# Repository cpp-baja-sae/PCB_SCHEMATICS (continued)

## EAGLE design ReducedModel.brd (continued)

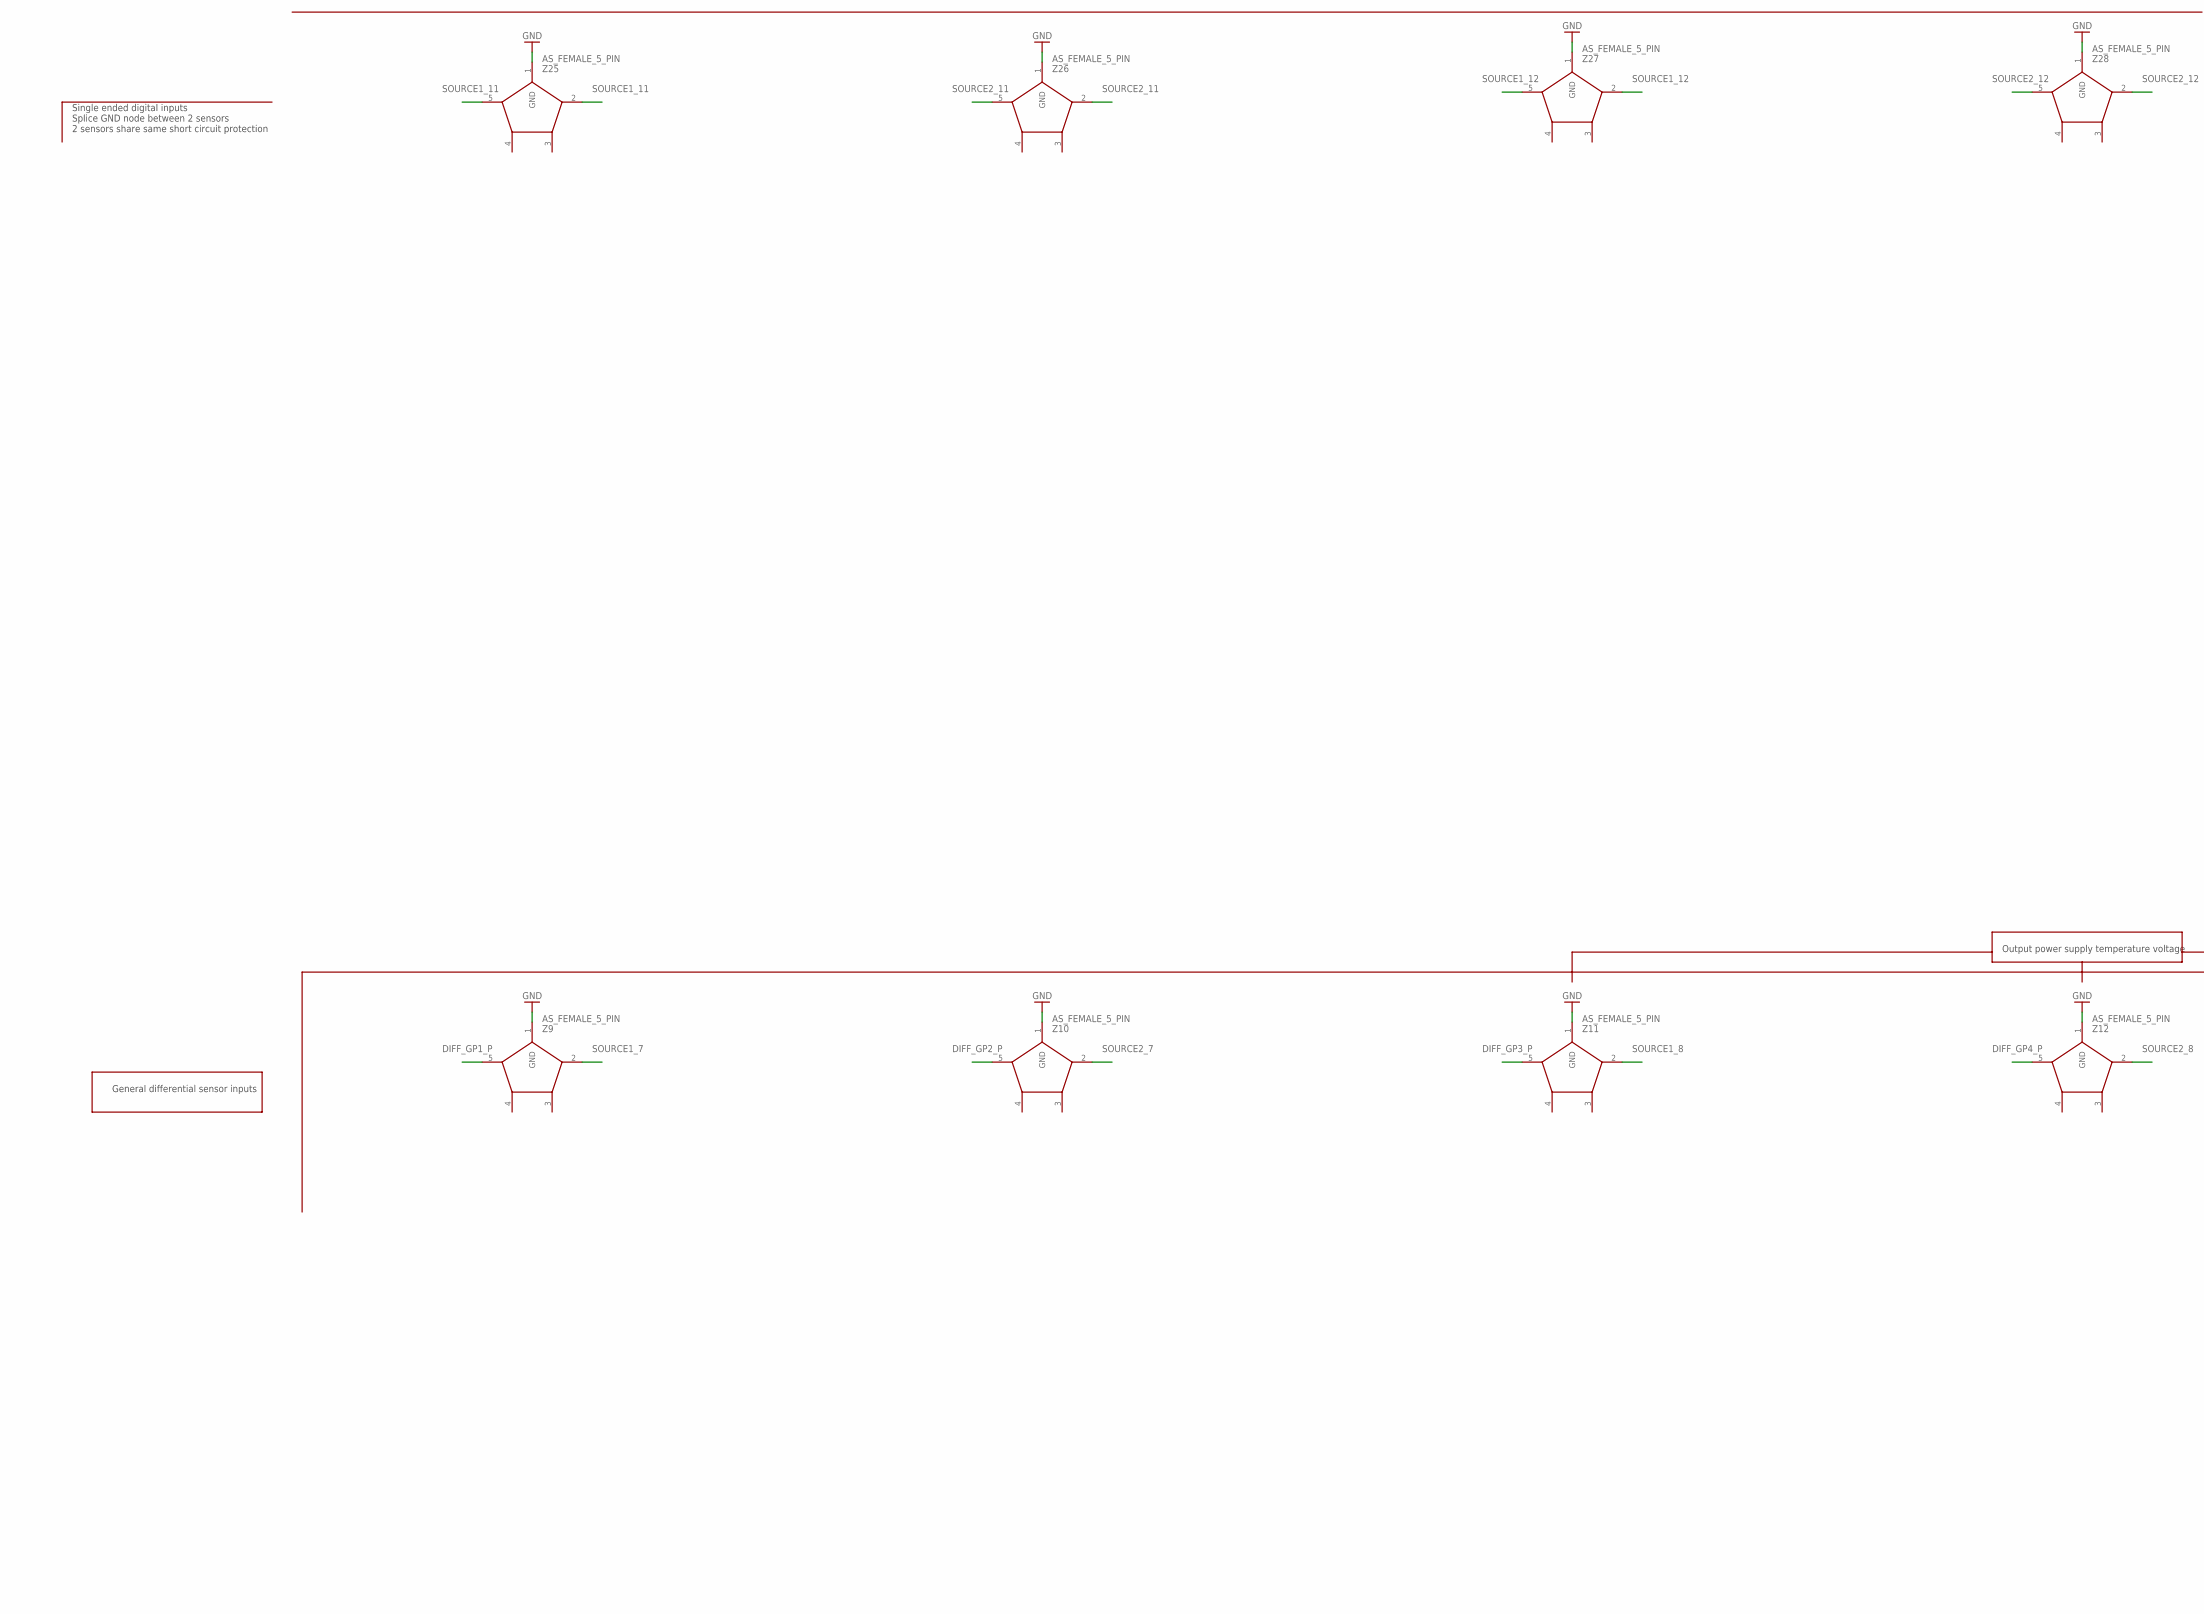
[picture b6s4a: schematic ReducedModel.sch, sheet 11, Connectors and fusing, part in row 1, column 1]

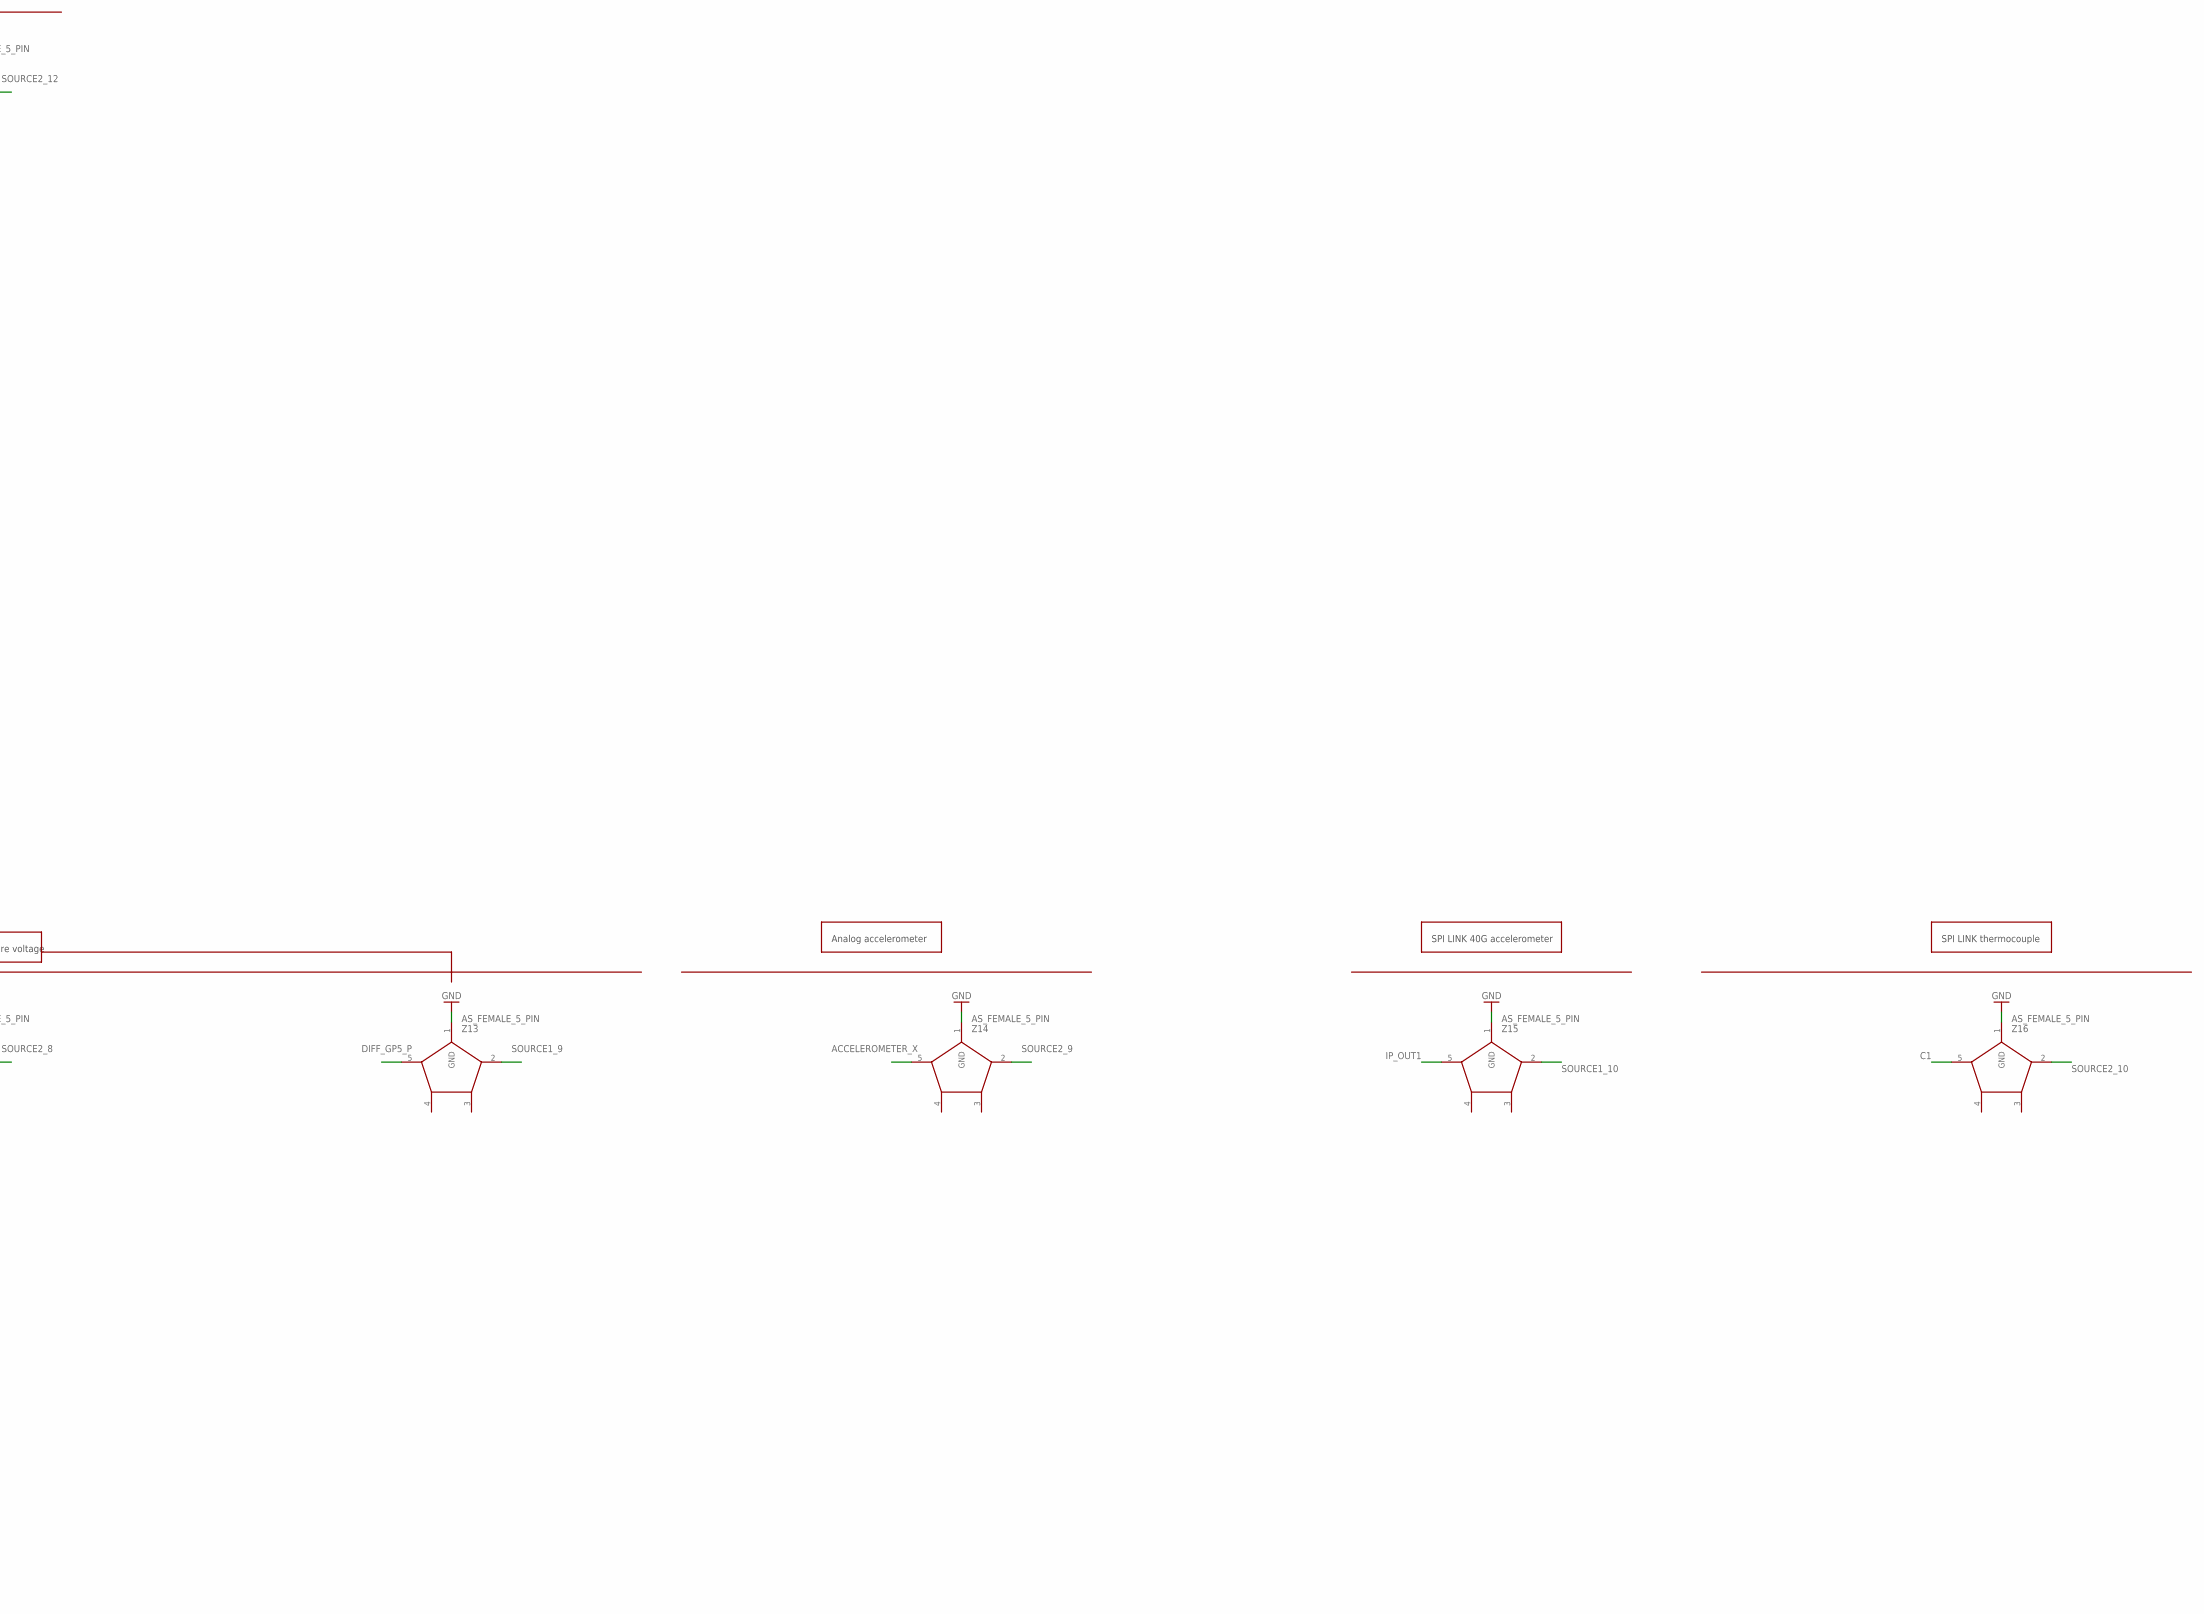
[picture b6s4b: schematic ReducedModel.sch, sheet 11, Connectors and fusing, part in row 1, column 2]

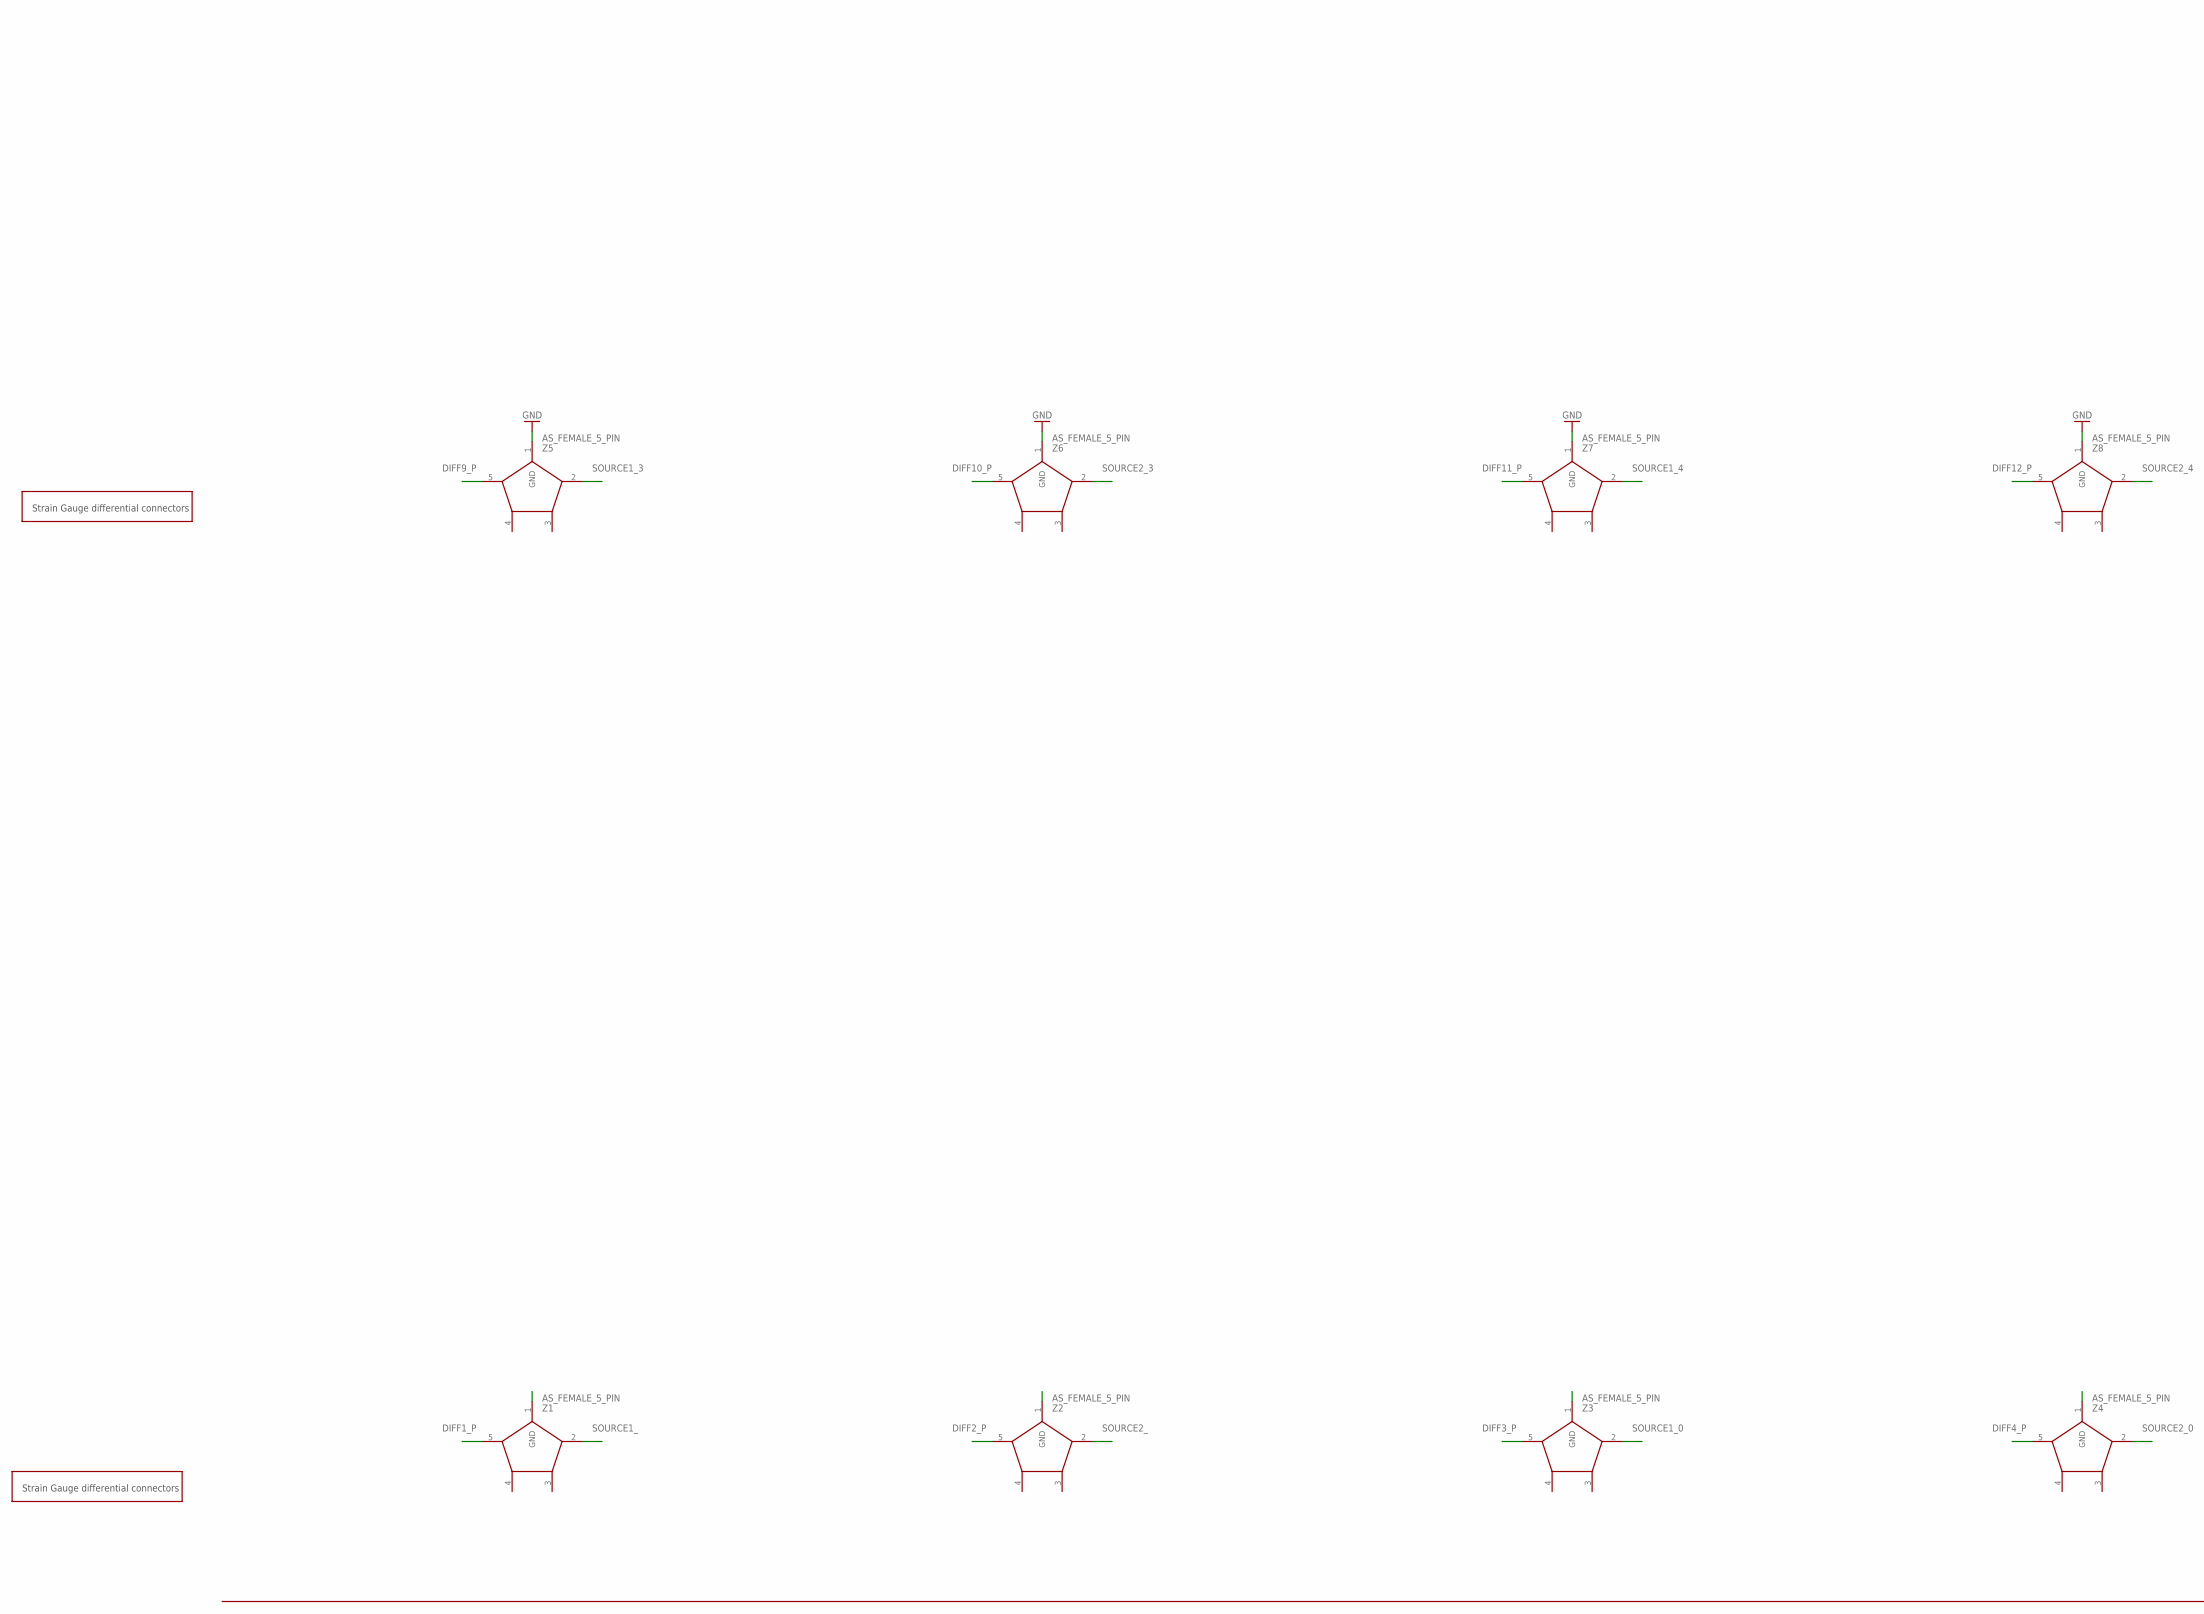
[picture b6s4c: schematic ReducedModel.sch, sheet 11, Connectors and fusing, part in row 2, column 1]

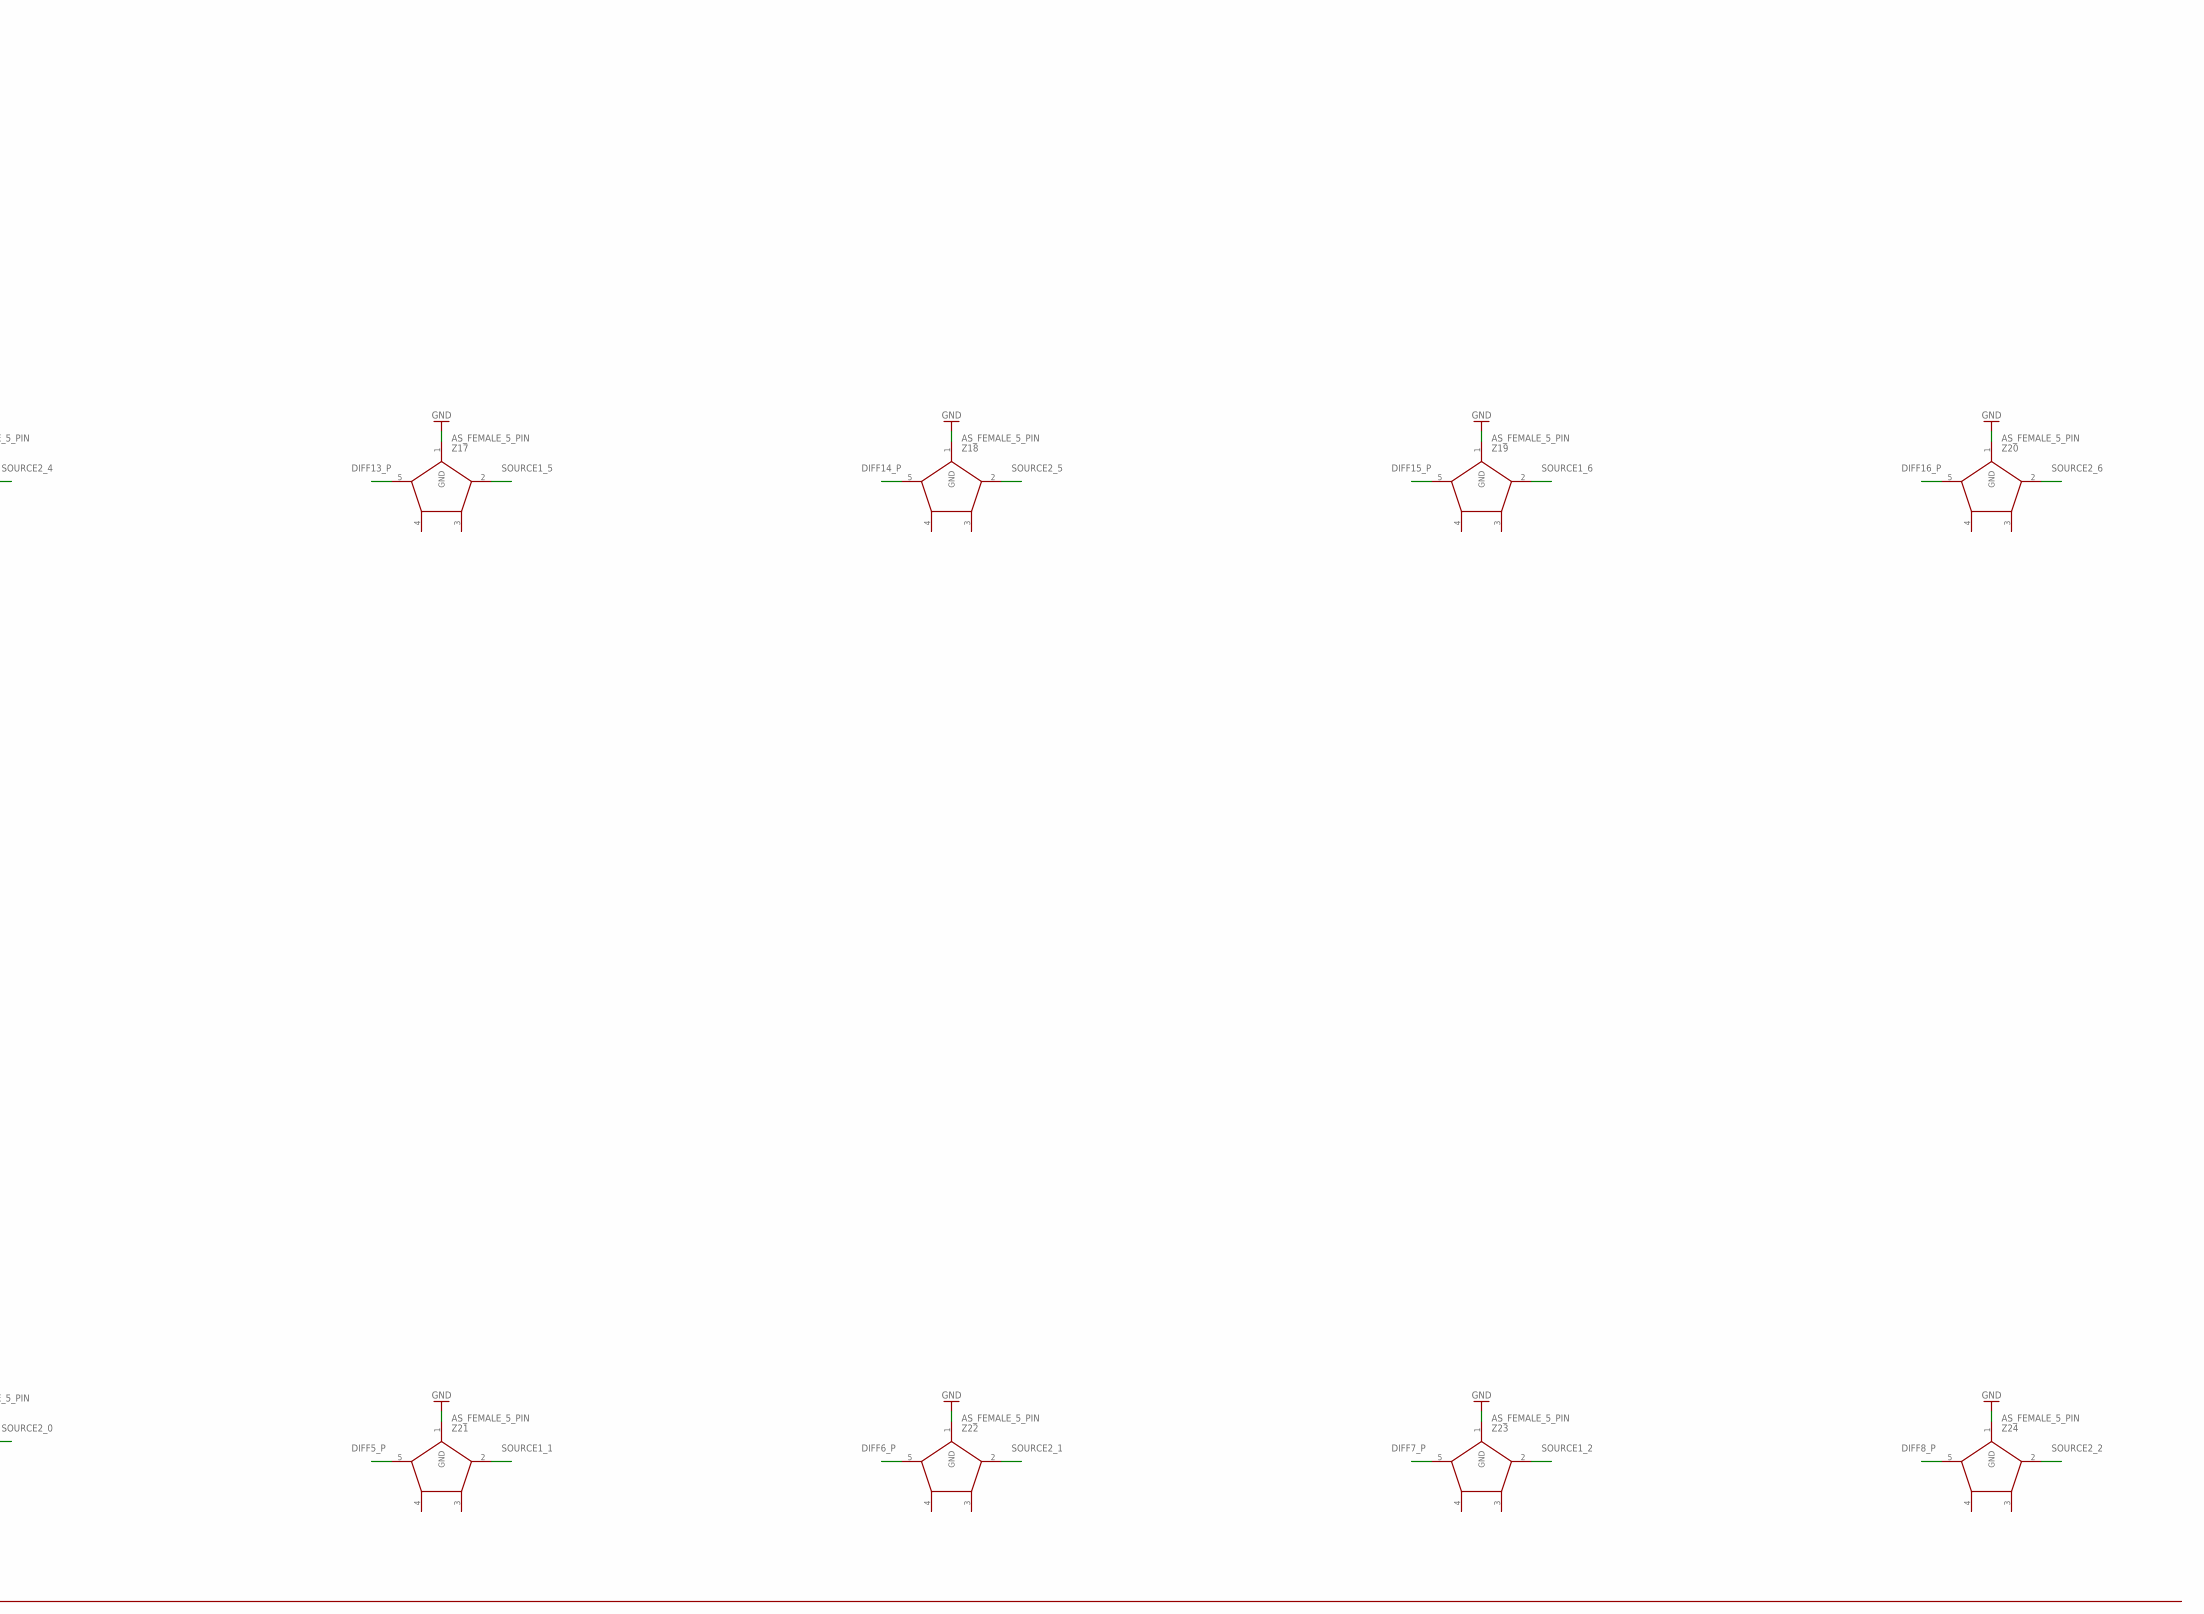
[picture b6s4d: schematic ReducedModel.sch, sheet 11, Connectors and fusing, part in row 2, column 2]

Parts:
Z1, Z2, Z3, Z4, Z5, Z6, Z7, Z8, Z9, Z10, Z11, Z12, Z13, Z14, Z15, Z16, Z17, Z18, Z19, Z20, Z21, Z22, Z23, Z24, Z25, Z26, Z27, Z28: AS_FEMALE_5_PIN

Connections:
ACCELEROMETER_X: Z14.5 (4)
C1: Z16.5 (4)
DIFF1_P: Z1.5 (4)
DIFF2_P: Z2.5 (4)
DIFF3_P: Z3.5 (4)
DIFF4_P: Z4.5 (4)
DIFF5_P: Z21.5 (4)
DIFF6_P: Z22.5 (4)
DIFF7_P: Z23.5 (4)
DIFF8_P: Z24.5 (4)
DIFF9_P: Z5.5 (4)
DIFF10_P: Z6.5 (4)
DIFF11_P: Z7.5 (4)
DIFF12_P: Z8.5 (4)
DIFF13_P: Z17.5 (4)
DIFF14_P: Z18.5 (4)
DIFF15_P: Z19.5 (4)
DIFF16_P: Z20.5 (4)
DIFF_GP1_P: Z9.5 (4)
DIFF_GP2_P: Z10.5 (4)
DIFF_GP3_P: Z11.5 (4)
DIFF_GP4_P: Z12.5 (4)
DIFF_GP5_P: Z13.5 (4)
GND: Z5.1 (GND), Z6.1 (GND), Z7.1 (GND), Z8.1 (GND), Z9.1 (GND), Z10.1 (GND), Z11.1 (GND), Z12.1 (GND), Z13.1 (GND), Z14.1 (GND), Z15.1 (GND), Z16.1 (GND), Z17.1 (GND), Z18.1 (GND), Z19.1 (GND), Z20.1 (GND), Z21.1 (GND), Z22.1 (GND), Z23.1 (GND), Z24.1 (GND), Z25.1 (GND), Z26.1 (GND), Z27.1 (GND), Z28.1 (GND); also elsewhere on the board
IP_OUT1: Z15.5 (4)
SOURCE1_: Z1.2 (1)
SOURCE1_0: Z3.2 (1)
SOURCE1_1: Z21.2 (1)
SOURCE1_2: Z23.2 (1)
SOURCE1_3: Z5.2 (1)
SOURCE1_4: Z7.2 (1)
SOURCE1_5: Z17.2 (1)
SOURCE1_6: Z19.2 (1)
SOURCE1_7: Z9.2 (1)
SOURCE1_8: Z11.2 (1)
SOURCE1_9: Z13.2 (1)
SOURCE1_10: Z15.2 (1)
SOURCE1_11: Z25.2 (1), Z25.5 (4)
SOURCE1_12: Z27.2 (1), Z27.5 (4)
SOURCE2_: Z2.2 (1)
SOURCE2_0: Z4.2 (1)
SOURCE2_1: Z22.2 (1)
SOURCE2_2: Z24.2 (1)
SOURCE2_3: Z6.2 (1)
SOURCE2_4: Z8.2 (1)
SOURCE2_5: Z18.2 (1)
SOURCE2_6: Z20.2 (1)
SOURCE2_7: Z10.2 (1)
SOURCE2_8: Z12.2 (1)
SOURCE2_9: Z14.2 (1)
SOURCE2_10: Z16.2 (1)
SOURCE2_11: Z26.2 (1), Z26.5 (4)
SOURCE2_12: Z28.2 (1), Z28.5 (4)

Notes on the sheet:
Strain Gauge differential connectors
General differential sensor inputs
Analog accelerometer
SPI LINK 40G accelerometer
SPI LINK thermocouple
Single ended digital inputs Splice GND node between 2 sensors 2 sensors share same short circuit protection
Output power supply temperature voltage

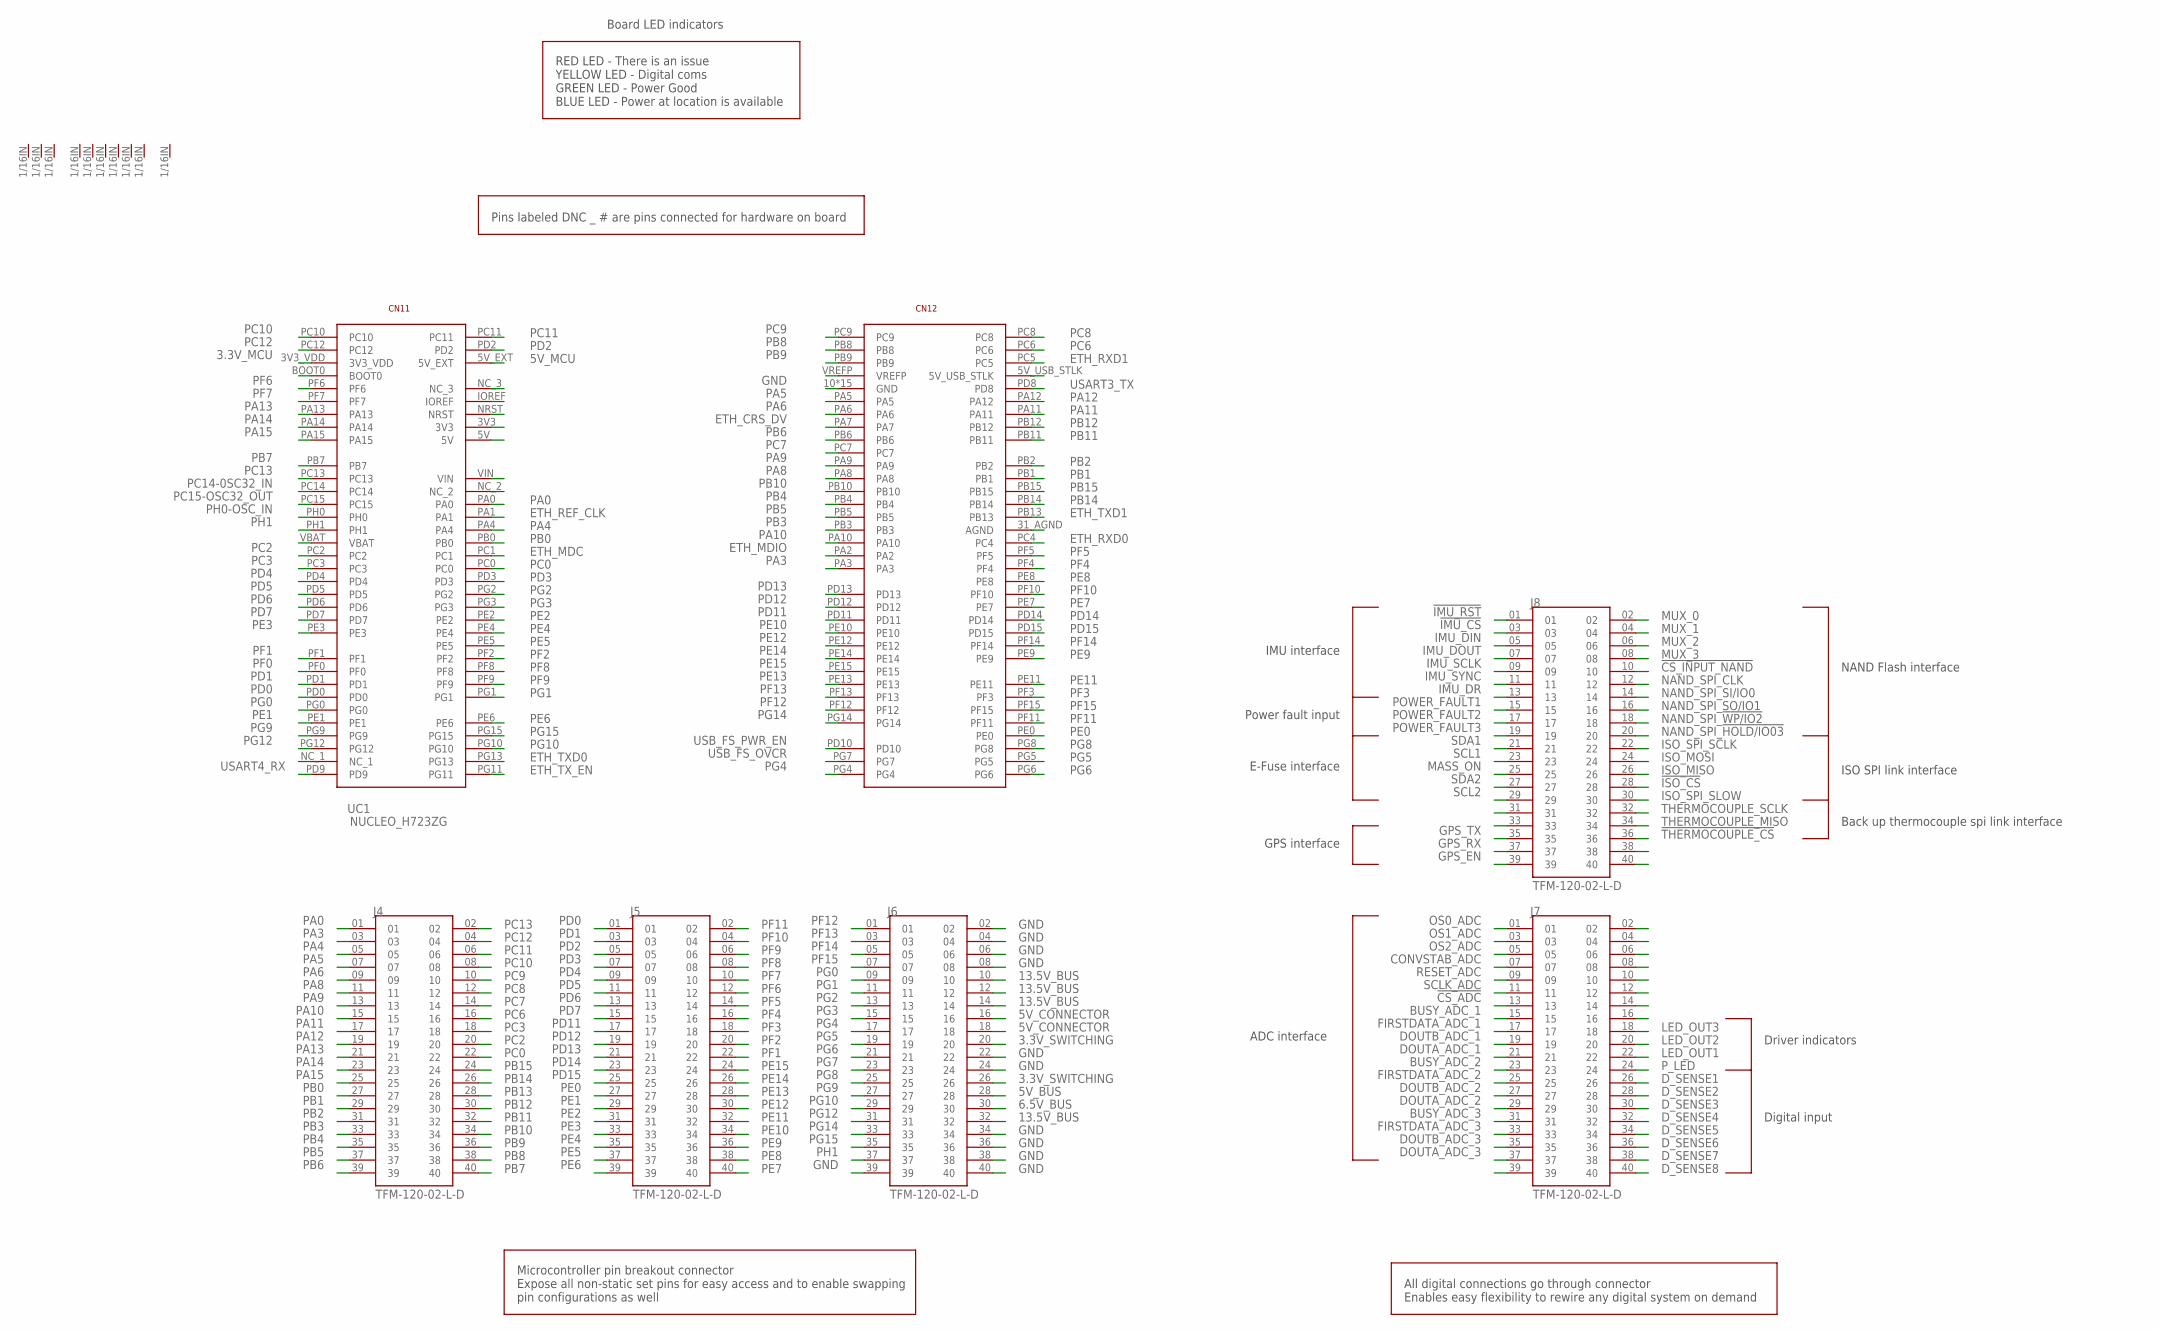
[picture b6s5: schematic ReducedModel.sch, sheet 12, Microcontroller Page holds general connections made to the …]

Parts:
J4, J5, J6, J7, J8: TFM-120-02-L-D; SAMTEC_TFM-120-02-L-D
U$5, U$6, U$7, U$8, U$9, U$10, U$12, U$13, U$14, U$15: THROUGH_HOLE; 1/16TH_BOLT
UC1: NUCLEO_H723ZG

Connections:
3.3V_MCU: UC1.3V3_VDD
3.3V_SWITCHING: J6.20, J6.26; also elsewhere on the board
5V_BUS: J6.28
5V_CONNECTOR: J6.16, J6.18
5V_MCU: UC1.5V_EXT
6.5V_BUS: J6.30
13.5V_BUS: J6.10, J6.12, J6.14, J6.32
!CS_ADC: J7.13
!CS_INPUT_NAND: J8.10
!IMU_CS: J8.03
!IMU_RST: J8.01
!ISO_CS: J8.28
!THERMOCOUPLE_CS: J8.36
BUSY_ADC_1: J7.15
BUSY_ADC_2: J7.23
BUSY_ADC_3: J7.31
CONVSTAB_ADC: J7.07
DOUTA_ADC_1: J7.21
DOUTA_ADC_2: J7.29
DOUTA_ADC_3: J7.37
DOUTB_ADC_1: J7.19
DOUTB_ADC_2: J7.27
DOUTB_ADC_3: J7.35
D_SENSE1: J7.26
D_SENSE2: J7.28
D_SENSE3: J7.30
D_SENSE4: J7.32
D_SENSE5: J7.34
D_SENSE6: J7.36
D_SENSE7: J7.38
D_SENSE8: J7.40
ETH_CRS_DV: UC1.PA7
ETH_MDC: UC1.PC1
ETH_MDIO: UC1.PA2
ETH_REF_CLK: UC1.PA1
ETH_RXD0: UC1.PC4
ETH_RXD1: UC1.PC5
ETH_TXD0: UC1.PG13
ETH_TXD1: UC1.PB13
ETH_TX_EN: UC1.PG11
FIRSTDATA_ADC_1: J7.17
FIRSTDATA_ADC_2: J7.25
FIRSTDATA_ADC_3: J7.33
GND: J6.02, J6.04, J6.06, J6.08, J6.22, J6.24, J6.34, J6.36, J6.38, J6.39, J6.40, UC1.10 (GND), UC1.19 (GND), UC1.40 (GND), UC1.53 (GND), UC1.64 (GND), UC1.71 (GND), UC1.72 (GND), UC1.79 (GND), UC1.91 (GND), UC1.92 (GND), UC1.93 (GND), UC1.122 (GND), UC1.131 (GND), UC1.143 (GND), UC1.144 (GND); also elsewhere on the board
GPS_EN: J8.39; also elsewhere on the board
GPS_RX: J8.37; also elsewhere on the board
GPS_TX: J8.35; also elsewhere on the board
IMU_DIN: J8.05
IMU_DOUT: J8.07
IMU_DR: J8.13
IMU_SCLK: J8.09
IMU_SYNC: J8.11
ISO_MISO: J8.26
ISO_MOSI: J8.24
ISO_SPI_SCLK: J8.22
ISO_SPI_SLOW: J8.30
LED_OUT1: J7.22
LED_OUT2: J7.20
LED_OUT3: J7.18
MASS_ON: J8.25
MUX_0: J8.02
MUX_1: J8.04
MUX_2: J8.06
MUX_3: J8.08
NAND_SPI_!HOLD/IO03: J8.20
NAND_SPI_!WP/IO2: J8.18
NAND_SPI_CLK: J8.12
NAND_SPI_SI/IO0: J8.14
NAND_SPI_SO/IO1: J8.16
OS0_ADC: J7.01
OS1_ADC: J7.03
OS2_ADC: J7.05
PA0: J4.01, UC1.PA0
PA3: J4.03, UC1.PA3
PA4: J4.05, UC1.PA4
PA5: J4.07, UC1.PA5
PA6: J4.09, UC1.PA6
PA8: J4.11, UC1.PA8
PA9: J4.13, UC1.PA9
PA10: J4.15, UC1.PA10
PA11: J4.17, UC1.PA11
PA12: J4.19, UC1.PA12
PA13: J4.21, UC1.PA13
PA14: J4.23, UC1.PA14
PA15: J4.25, UC1.PA15
PB0: J4.27, UC1.PB0
PB1: J4.29, UC1.PB1
PB2: J4.31, UC1.PB2
PB3: J4.33, UC1.PB3
PB4: J4.35, UC1.PB4
PB5: J4.37, UC1.PB5
PB6: J4.39, UC1.PB6
PB7: J4.40, UC1.PB7
PB8: J4.38, UC1.PB8
PB9: J4.36, UC1.PB9
PB10: J4.34, UC1.PB10
PB11: J4.32, UC1.PB11
PB12: J4.30, UC1.PB12
PB13: J4.28
PB14: J4.26, UC1.PB14
PB15: J4.24, UC1.PB15
PC0: J4.22, UC1.PC0
PC2: J4.20, UC1.PC2
PC3: J4.18, UC1.PC3
PC6: J4.16, UC1.PC6
PC7: J4.14, UC1.PC7
PC8: J4.12, UC1.PC8
PC9: J4.10, UC1.PC9
PC10: J4.08, UC1.PC10
PC11: J4.06, UC1.PC11
PC12: J4.04, UC1.PC12
PC13: J4.02, UC1.PC13
PC14-0SC32_IN: UC1.PC14
PC15-OSC32_OUT: UC1.PC15
PD0: J5.01, UC1.PD0
PD1: J5.03, UC1.PD1
PD2: J5.05, UC1.PD2
PD3: J5.07, UC1.PD3
PD4: J5.09, UC1.PD4
PD5: J5.11, UC1.PD5
PD6: J5.13, UC1.PD6
PD7: J5.15, UC1.PD7
PD11: J5.17, UC1.PD11
PD12: J5.19, UC1.PD12
PD13: J5.21, UC1.PD13
PD14: J5.23, UC1.PD14
PD15: J5.25, UC1.PD15
PE0: J5.27, UC1.PE0
PE1: J5.29, UC1.PE1
PE2: J5.31, UC1.PE2
PE3: J5.33, UC1.PE3
PE4: J5.35, UC1.PE4
PE5: J5.37, UC1.PE5
PE6: J5.39, UC1.PE6
PE7: J5.40, UC1.PE7
PE8: J5.38, UC1.PE8
PE9: J5.36, UC1.PE9
PE10: J5.34, UC1.PE10
PE11: J5.32, UC1.PE11
PE12: J5.30, UC1.PE12
PE13: J5.28, UC1.PE13
PE14: J5.26, UC1.PE14
PE15: J5.24, UC1.PE15
PF0: UC1.PF0
PF1: J5.22, UC1.PF1
PF2: J5.20, UC1.PF2
PF3: J5.18, UC1.PF3
PF4: J5.16, UC1.PF4
PF5: J5.14, UC1.PF5
PF6: J5.12, UC1.PF6
PF7: J5.10, UC1.PF7
PF8: J5.08, UC1.PF8
PF9: J5.06, UC1.PF9
PF10: J5.04, UC1.PF10
PF11: J5.02, UC1.PF11
PF12: J6.01, UC1.PF12
PF13: J6.03, UC1.PF13
PF14: J6.05, UC1.PF14
PF15: J6.07, UC1.PF15
PG0: J6.09, UC1.PG0
PG1: J6.11, UC1.PG1
PG2: J6.13, UC1.PG2
PG3: J6.15, UC1.PG3
PG4: J6.17, UC1.PG4
PG5: J6.19, UC1.PG5
PG6: J6.21, UC1.PG6
PG7: J6.23
PG8: J6.25, UC1.PG8
PG9: J6.27, UC1.PG9
PG10: J6.29, UC1.PG10
PG12: J6.31, UC1.PG12
PG14: J6.33, UC1.PG14
PG15: J6.35, UC1.PG15
PH0-OSC_IN: UC1.PH0
PH1: J6.37, UC1.PH1
POWER_FAULT1: J8.15; also elsewhere on the board
POWER_FAULT2: J8.17; also elsewhere on the board
POWER_FAULT3: J8.19; also elsewhere on the board
P_LED: J7.24
RESET_ADC: J7.09
SCL1: J8.23
SCL2: J8.29
SCLK_ADC: J7.11
SDA1: J8.21
SDA2: J8.27
THERMOCOUPLE_MISO: J8.34
THERMOCOUPLE_SCLK: J8.32
USART3_TX: UC1.PD8
USART4_RX: UC1.PD9
USB_FS_OVCR: UC1.PG7
USB_FS_PWR_EN: UC1.PD10

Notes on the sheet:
Pins labeled DNC _ # are pins connected for hardware on board
RED LED - There is an issue YELLOW LED - Digital coms GREEN LED - Power Good BLUE LED - Power at location is available
Board LED indicators
Microcontroller pin breakout connector Expose all non-static set pins for easy access and to enable swapping pin configurations as well
All digital connections go through connector Enables easy flexibility to rewire any digital system on demand
NAND Flash interface
ISO SPI link interface
Back up thermocouple spi link interface
GPS interface
IMU interface
Power fault input
E-Fuse interface
Digital input
Driver indicators
ADC interface

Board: 2 copper layers, 47 parts (6 on the bottom side), 111 nets, no tracks yet.
